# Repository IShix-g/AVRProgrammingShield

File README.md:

AVR マイコンにスケッチを書き込む為のシールドです。
書き込み方式はISPとなります。

# 使い方

## 1. Arduino Pro Microを設置

## 2. AVRマイコンを設置
レバー側を上として上に詰めるようにAVRマイコンを配置しレーバーを倒します。

## 3. ジャンパーケーブルを接続
すべてのピンにジャンパーケーブルを接続します。

## 4. AVRマイコンに合わせてジャンパーケーブルを接続
2のソケット左右に書かれた1-20の番号と4の1-20の番号は内部で接続されています。
例えば2のソケットの1番は、4の1と繋がっています。
3で接続したジャンパーピンをマイコンのデータシートを見ながら4の必要な番号に接続します。

### [接続例] ATiny2313

| シールド | ATiny2313  |
|------|-----|
| VCC  | 20  |
| MOSI | 17  |
| GND  | 10  |
| MISO | 18  |
| SCK  | 19  |
| RST  | 1   |

## 5. LEDのテスト用ピン
LEDで正常に書き込めるかテストができます。

## 6. 外部出力
4の1-20と内部で接続されています。ブレッドボードなどと接続する用途で使えます。

## 7. リセットボタン

# 必要なパーツ

| リファレンス  | 名前                    | サイズ/容量                 | 数   |
|---------|-----------------------|------------------------|-----|
| U1      | Arduino Pro Micro     |                        | 1   |
| C1      | セラミックコンデンサ            | 104 (0.1uF)            | 1   |
| C2      | 電解コンデンサ               | 10uF                   | 1   |
| D1-D4   | LED              | 3mm 5V                 | 4   |
| U2      | ZIF ソケット  | 2.54mmピッチ 20pin 300mil | 1   |
| R1-R4   | カーボン抵抗                | 300Ω前後                 | 4   |
| SW1,Sw2 | タクトスイッチ            | 5mm                    | 2   |
| J1      | ピンソケット      | 2.54mmピッチ 2x10         | 2   |
| J2      | ピンソケット      | 2.54mmピッチ 1x12         | 2   |
| J3      | ピンヘッダー      | 2.54mmピッチ 2x3          | 1   |
| J4      | ピンヘッダー      | 2.54mmピッチ 1x1          | 1   |

# その他の必要なもの

- ジャンパーケーブル(メス、オス) x 7

# スケッチの書き込み

## [初回のみ] Arduino Pro MicroにArduinoISPを書き込む

**File > Examples > 11.ArduinoISP**

普段通りスケッチを開いてアップロードボタンを押すだけです。
このシールドに載せたままでは書き込みできないので、載せずに書き込みしてください。

## [初回のみ] ブートローダーを書き込みする
ブートローダーを書き込む為ではなく、クロック数を合わせる為に必要なようです。

## プログラマにArduino as ISPを選択する

## スケッチの書き込みの際はプログラマーを使ってアップロードで書き込みする

# 基板の発注
[PCBWay](https://www.pcbway.jp/g/ug57q0)に注文する場合、対応するGerber Fileを利用できます。

- [ProgrammingShield V1.0.kicad_pcb.zip](ProgrammingShield V1.0.kicad_pcb.zip)

## 修正したい場合
KiCad 7のデータがそのまま含まれています。ダウンロードして自由に修正してください。
開く前に下記2つのデータをインストールする必要があります。

- [ArduinoのKiCAD用ライブラリ公開](https://www.g200kg.com/archives/2020/11/arduinokicad.html)
- [kicad用ゼロプレッシャーICソケットの部品](http://ayabu.blog.shinobi.jp/kicad/kicad%E7%94%A8%E3%82%BC%E3%83%AD%E3%83%97%E3%83%AC%E3%83%83%E3%82%B7%E3%83%A3%E3%83%BCic%E3%82%BD%E3%82%B1%E3%83%83%E3%83%88%E3%81%AE%E9%83%A8%E5%93%81)

## 修正した後に基板を発注したい場合

[PCBWay](https://www.pcbway.jp/g/ug57q0)に注文する場合、プラグイン&コンテンツマネージャーよりPCBWayのプラグインを導入するとワンクリックでGerber Fileの生成とzip圧縮、注文画面へのzip貼り付けを自動でやってくれるので便利です。

# 動作確認済み AVRマイコン
- ATtiny 13A
- ATtiny 44A
- ATtiny 84A
- ATtiny 2313

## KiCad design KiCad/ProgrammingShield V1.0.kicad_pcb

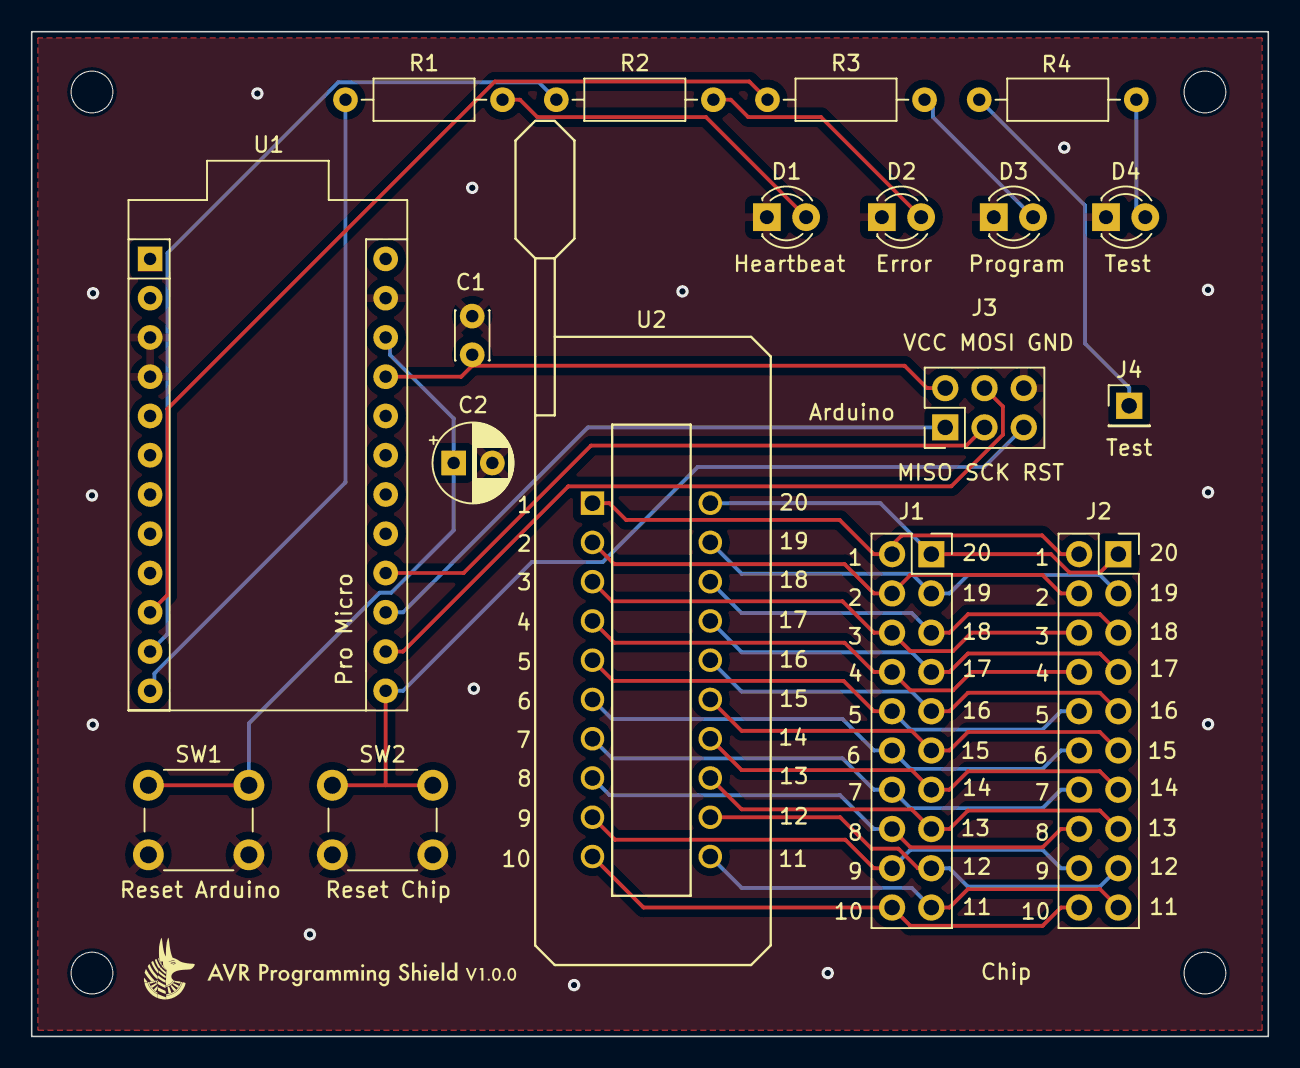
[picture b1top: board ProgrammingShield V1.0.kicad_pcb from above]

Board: 2 copper layers, 80.0 x 65.0 mm, 22 parts (0 on the bottom side), 35 nets.

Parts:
C1: 0.1uF; C_Disc_D3.0mm_W2.0mm_P2.50mm
C2: 10uF; CP_Radial_D5.0mm_P2.50mm
D1: Heartbeat; LED_D3.0mm
D2: Error; LED_D3.0mm
D3: Program; LED_D3.0mm
D4: Test; LED_D3.0mm
H1, H2, H3, H4: MountingHole; MountingHole_2.7mm_M2.5
J1: 1-10; PinSocket_2x10_P2.54mm_Vertical
J2: 11-20; PinSocket_2x10_P2.54mm_Vertical
J3: ICSP Out; PinHeader_2x03_P2.54mm_Vertical
J4: Test; PinHeader_1x01_P2.54mm_Vertical
R1, R2, R3, R4: 300; R_Axial_DIN0207_L6.3mm_D2.5mm_P10.16mm_Horizontal
SW1: Reset Arduino; SW_PUSH_6mm
SW2: Reset Chip; SW_PUSH_6mm
U1: Pro Micro; Sparkfun_Pro_Micro
U2: 220-3345; 220-3342

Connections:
+5V: C1.1, J3.2 (VCC), U1.21 (VCC)
/7: R3.1, U1.10 (D7)
/8: R2.1, U1.11 (D8/A8)
/9: R1.1, U1.12 (~D9/A9)
/C1: J1.2, J2.2, U2.1
/C2: J1.4, J2.4, U2.2
/C3: J1.6, J2.6, U2.3
/C4: J1.8, J2.8, U2.4
/C5: J1.10, J2.10, U2.5
/C6: J1.12, J2.12, U2.6
/C7: J1.14, J2.14, U2.7
/C8: J1.16, J2.16, U2.8
/C9: J1.18, J2.18, U2.9
/C10: J1.20, J2.20, U2.10
/C11: J1.19, J2.19, U2.11
/C12: J1.17, J2.17, U2.12
/C13: J1.15, J2.15, U2.13
/C14: J1.13, J2.13, U2.14
/C15: J1.11, J2.11, U2.15
/C16: J1.9, J2.9, U2.16
/C17: J1.7, J2.7, U2.17
/C18: J1.5, J2.5, U2.18
/C19: J1.3, J2.3, U2.19
/C20: J1.1, J2.1, U2.20
/MISO: J3.1 (MISO), U1.15 (D14)
/MOSI: J3.4 (MOSI), U1.14 (D16)
/RST: J3.5 (~RST), SW2.1 (A), U1.13 (~D10/A10)
/Reset: C2.1, SW1.1 (A), U1.22 (RST)
/SCK: J3.3 (SCK), U1.16 (D15)
/Test: J4.1, R4.1
GND: C1.2, C2.2, D1.1 (K), D2.1 (K), D3.1 (K), D4.1 (K), J3.6 (GND), SW1.2 (A), SW2.2 (A), U1.3 (GND), U1.4 (GND), U1.23 (GND)
unnamed: D1.2 (A), R1.2
unnamed: D2.2 (A), R2.2
unnamed: D3.2 (A), R3.2
unnamed: D4.2 (A), R4.2

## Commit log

2023-04-02 KiCadデータなど追加
